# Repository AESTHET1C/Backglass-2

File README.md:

# Backglass 2 Pinball Controller Board

An Arduino Uno-compatible unified control board tailored to the Eli Whitney Museum 2017 summer pinball project.

The board contains the following hardware:

* Microchip ATmega8U2/16U2 (serial communication and code upload)
* Microchip ATmega328P (user code)
* Microchip ATmega48PB (audio/visual coprocessing)
* 4-character 7 segment display
* 2 analogue inputs (for reflectance sensors)
* 5 digital inputs (with integrated pull-ups)
* 3 current-limited LED outputs
* 1 PWM-controlled motor output
* 1 speaker output
* Micro USB interface
* 2.7 - 6.5 volt power input

All features of the board, with the exception of the motor, can be powered via USB.

-----

A user-oriented code library can be found here: <https://github.com/AESTHET1C/Backglass-2-Library/>

The coprocessor firmware can be found here: <https://github.com/AESTHET1C/Backglass-2-Firmware/>

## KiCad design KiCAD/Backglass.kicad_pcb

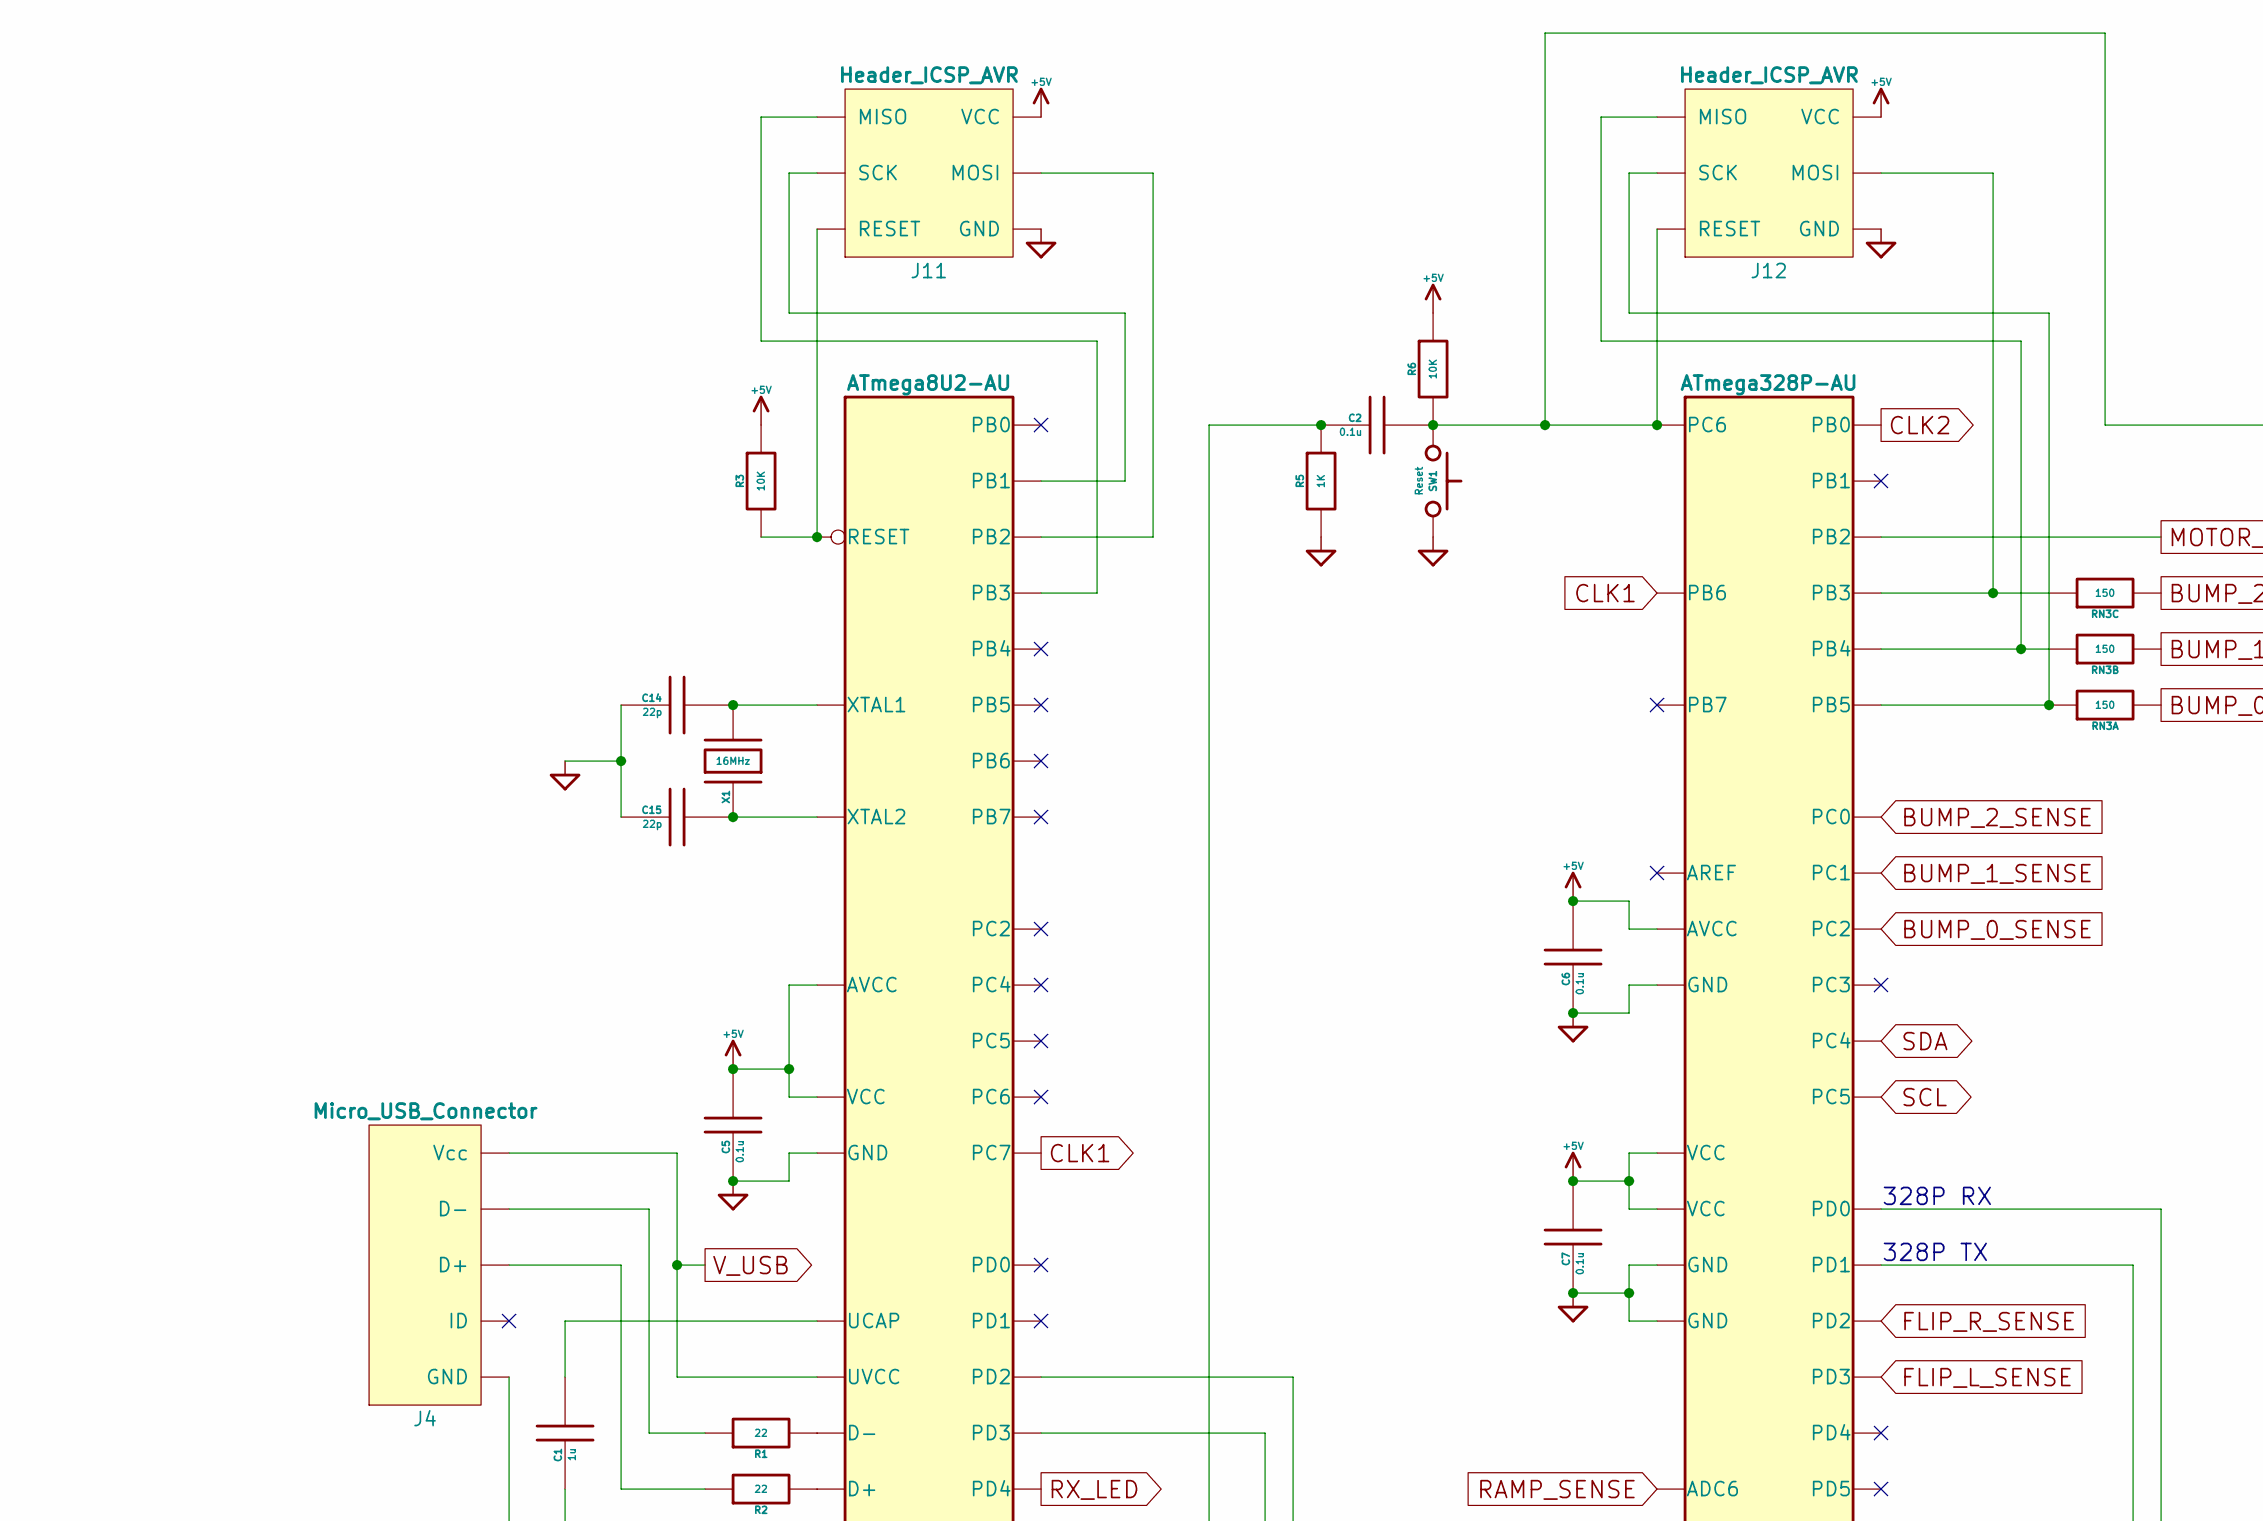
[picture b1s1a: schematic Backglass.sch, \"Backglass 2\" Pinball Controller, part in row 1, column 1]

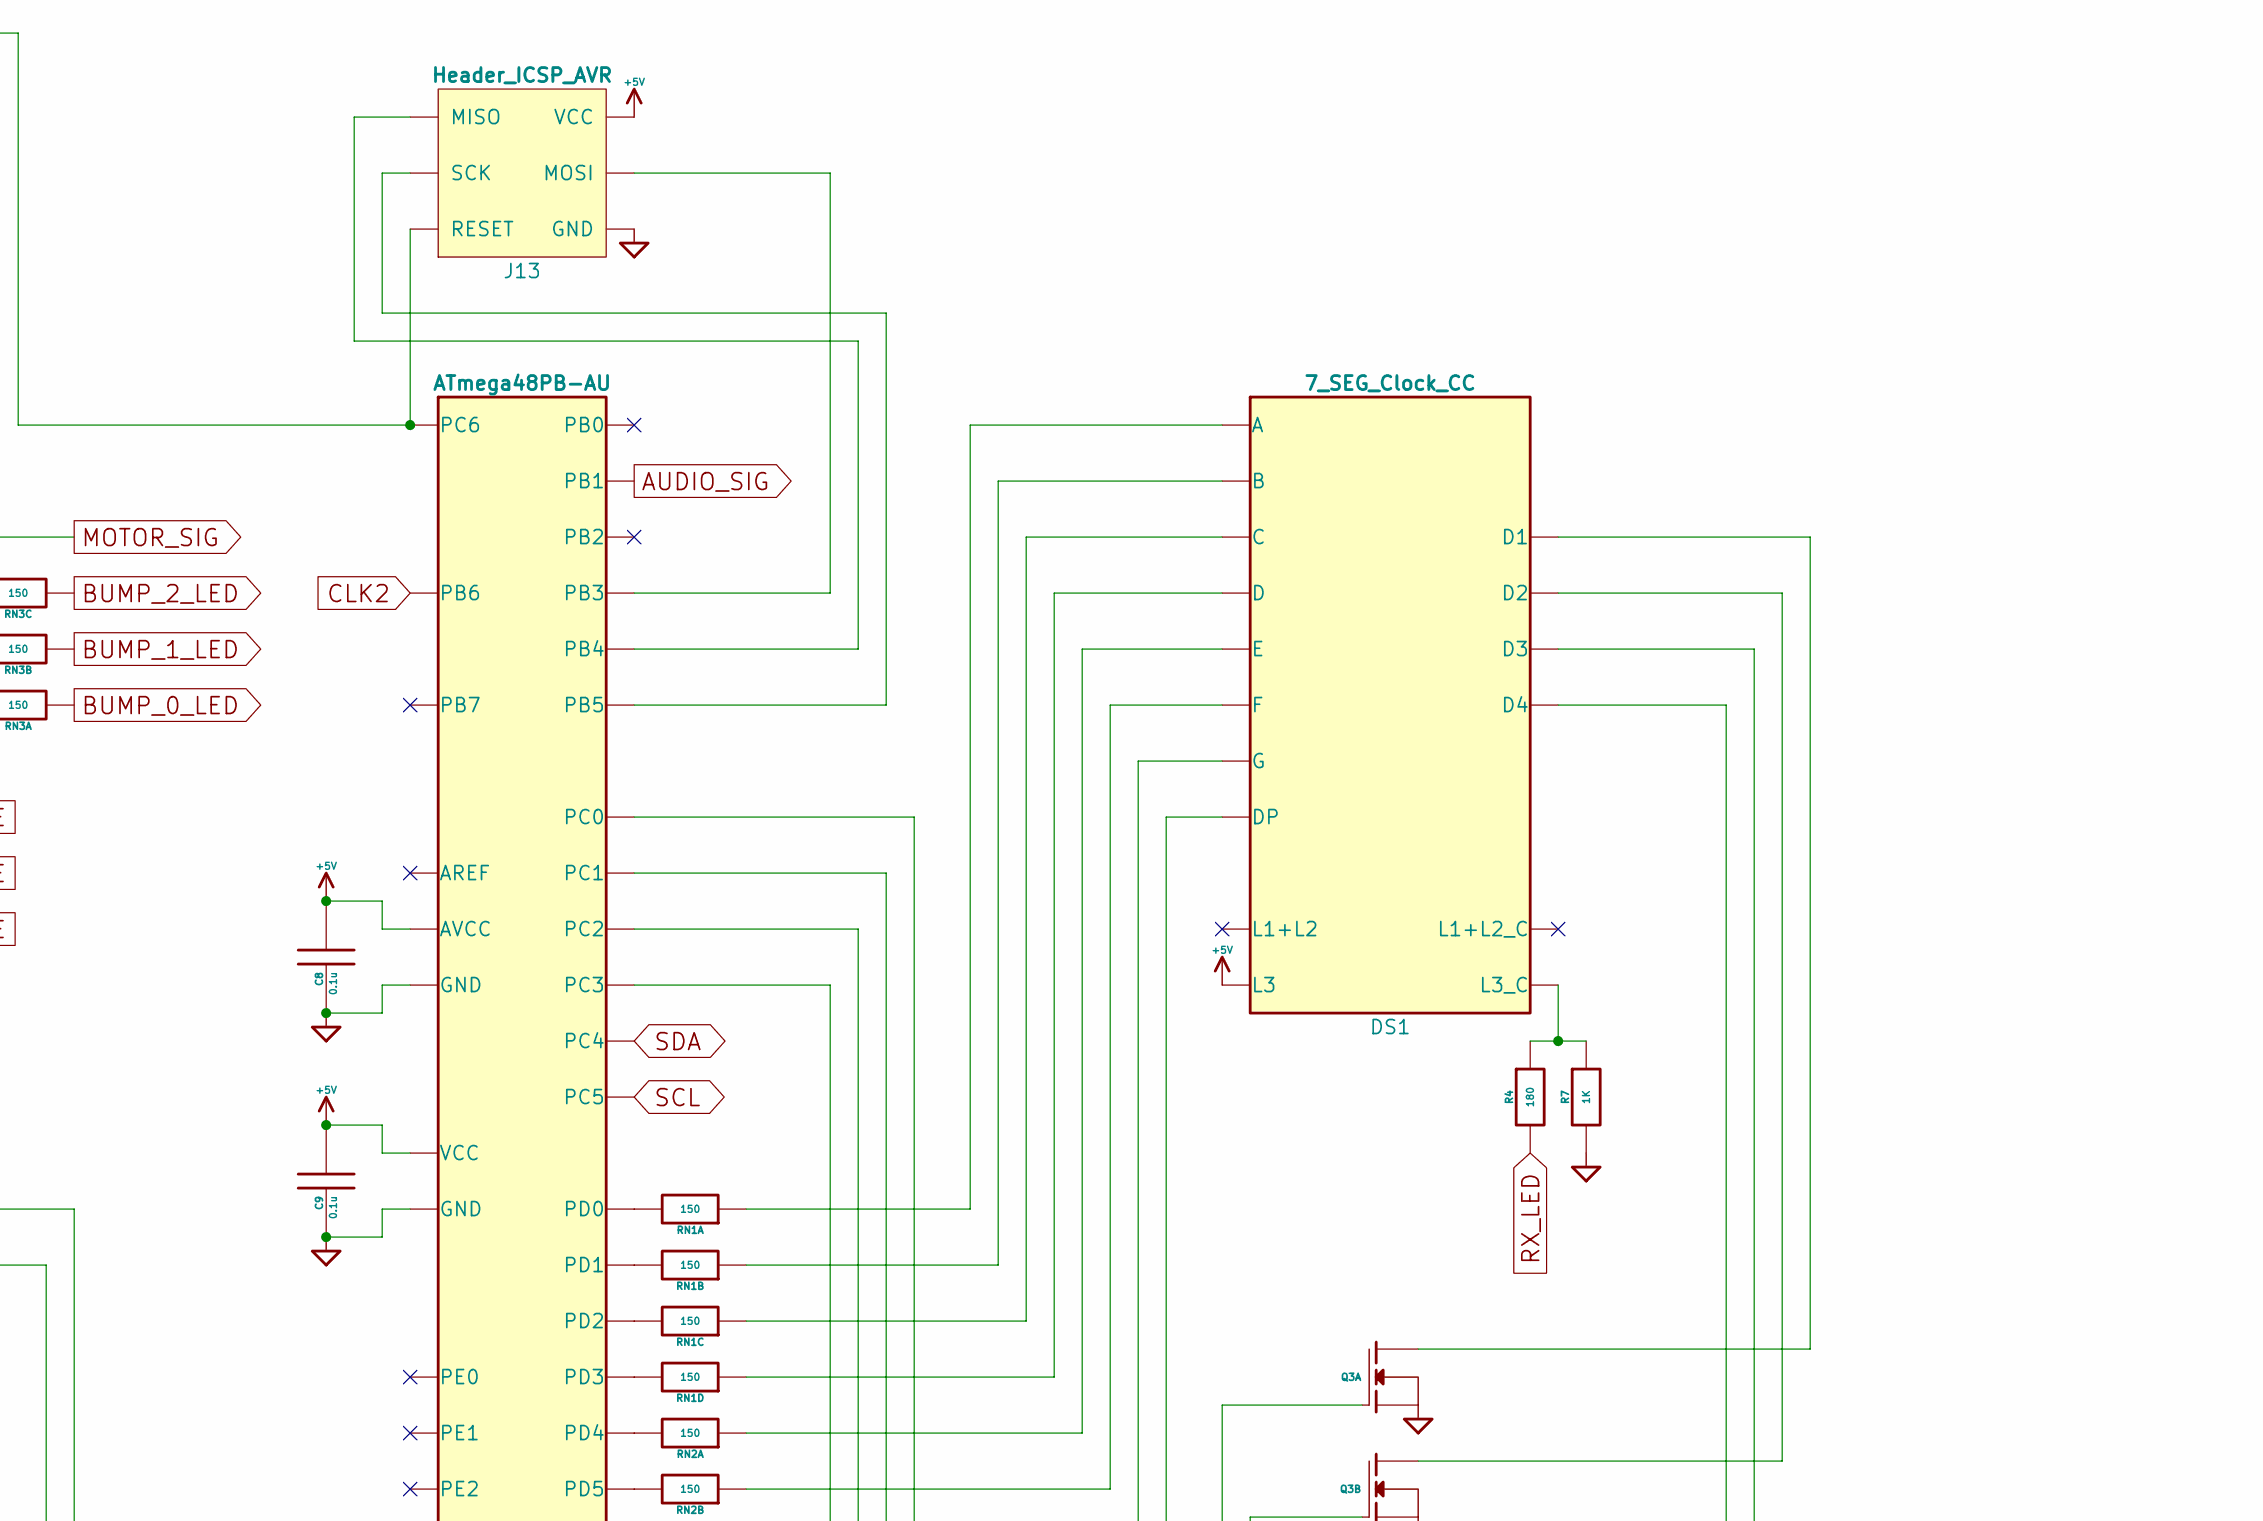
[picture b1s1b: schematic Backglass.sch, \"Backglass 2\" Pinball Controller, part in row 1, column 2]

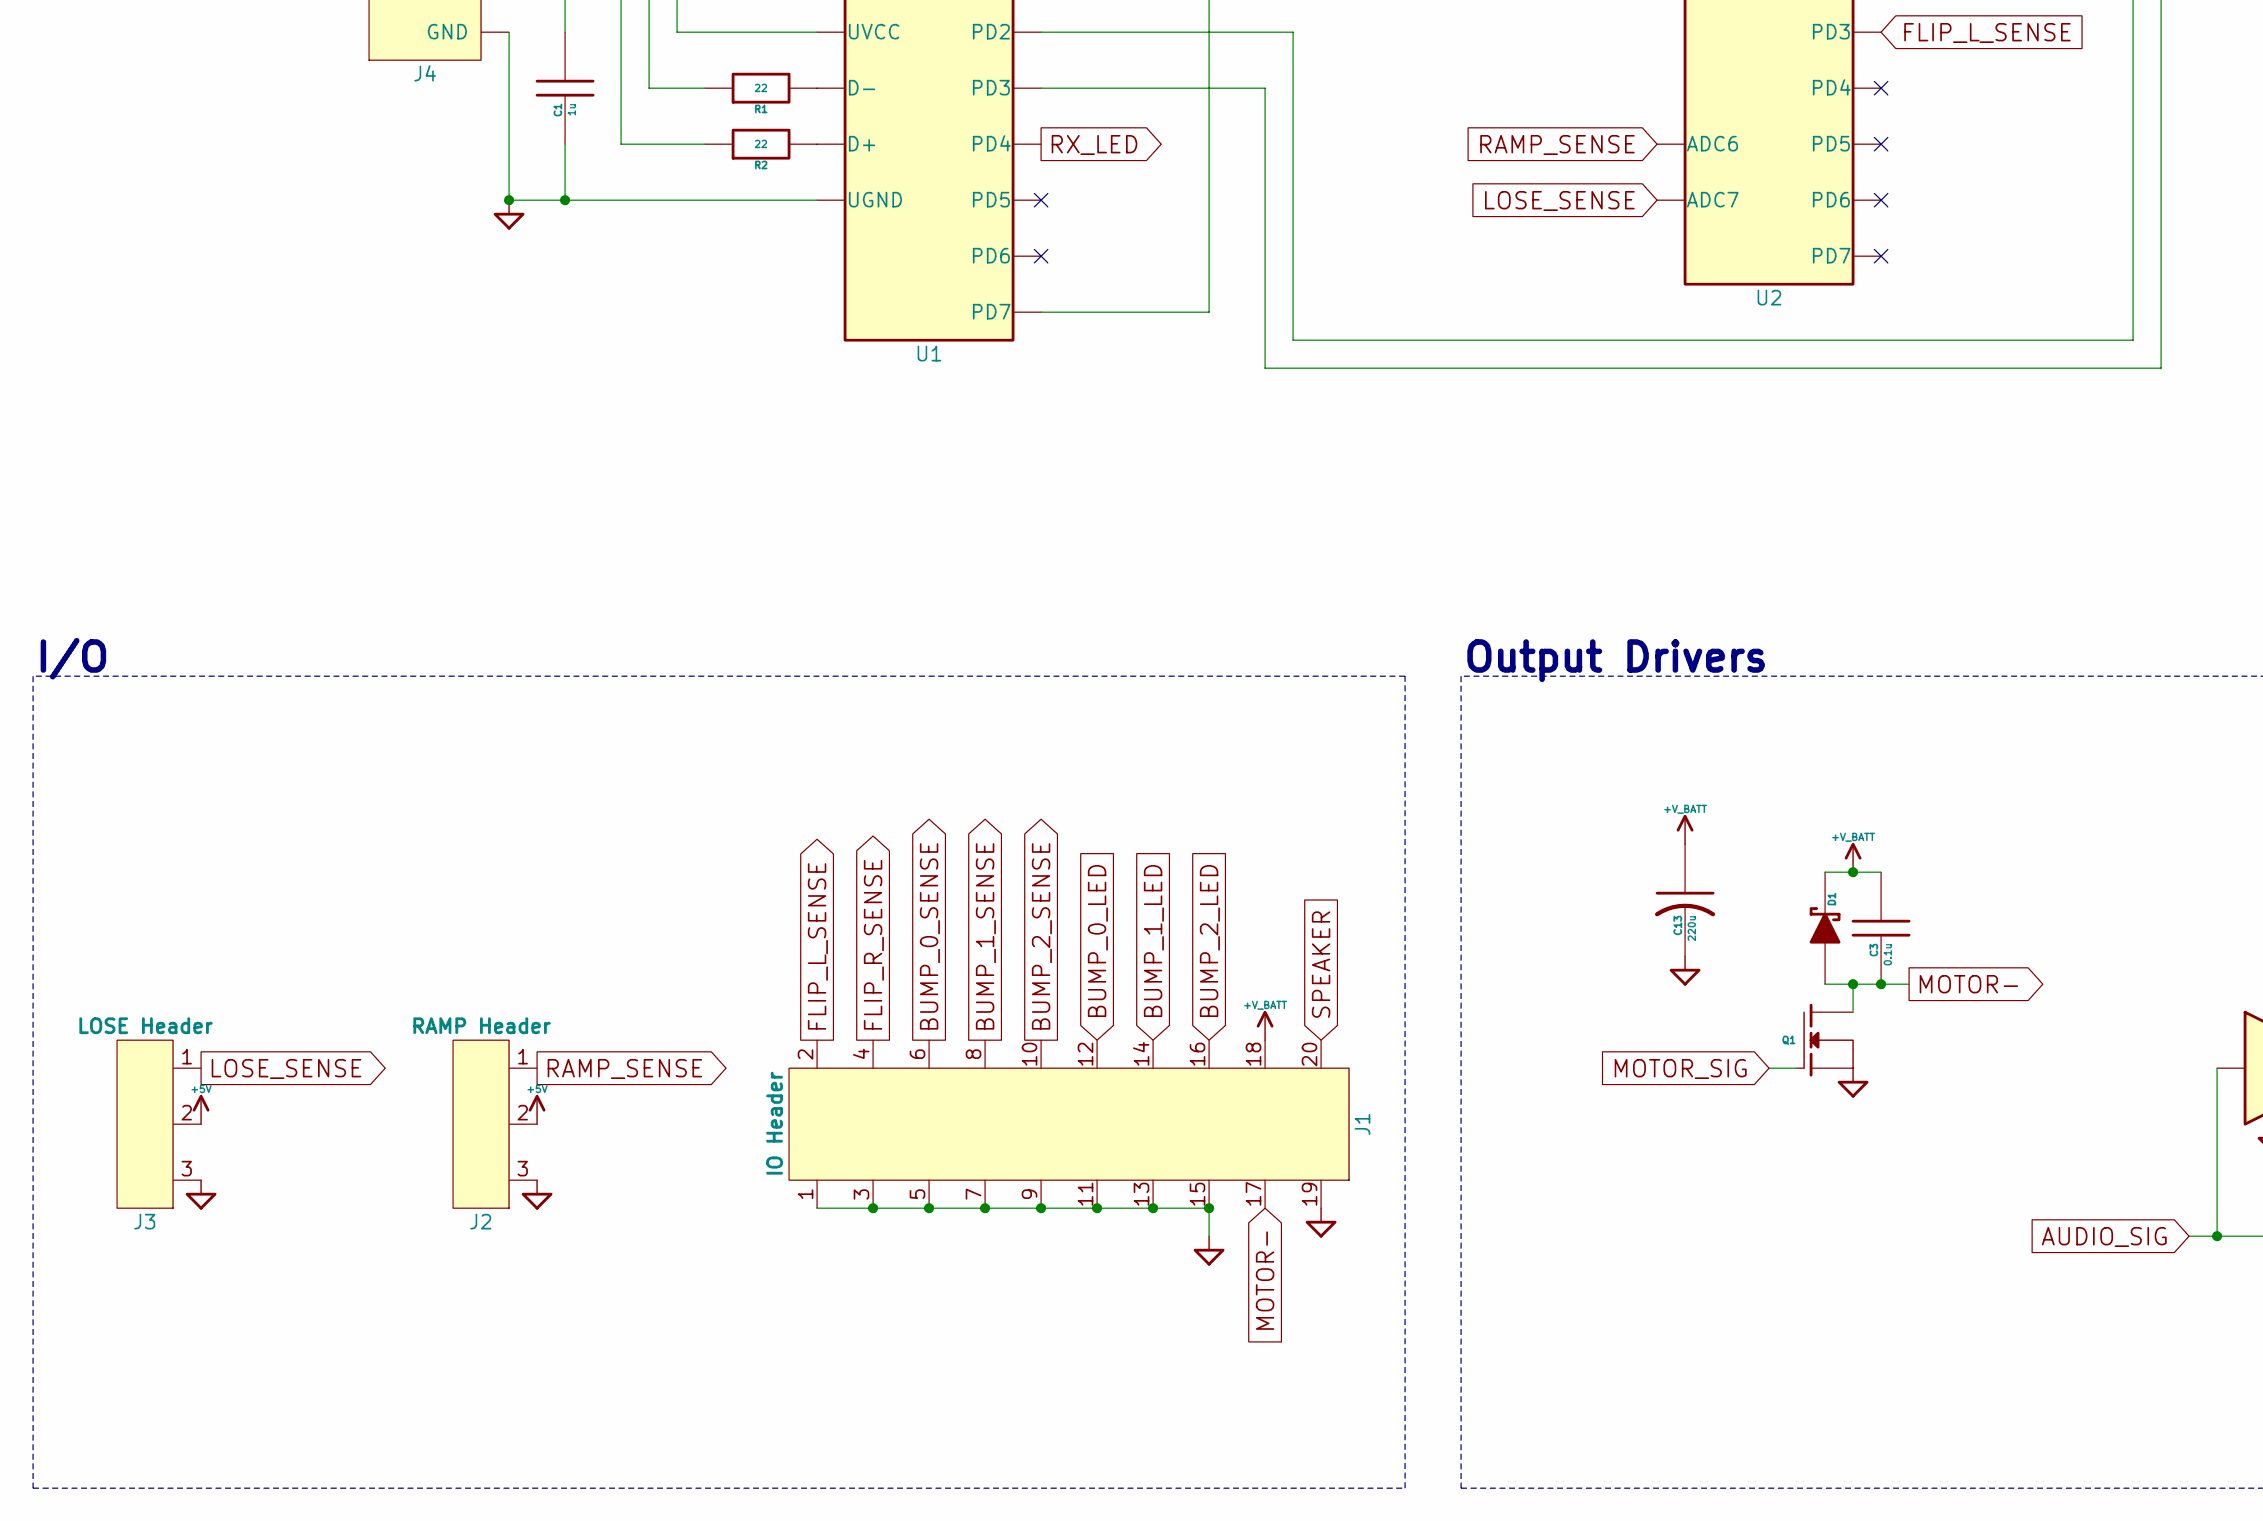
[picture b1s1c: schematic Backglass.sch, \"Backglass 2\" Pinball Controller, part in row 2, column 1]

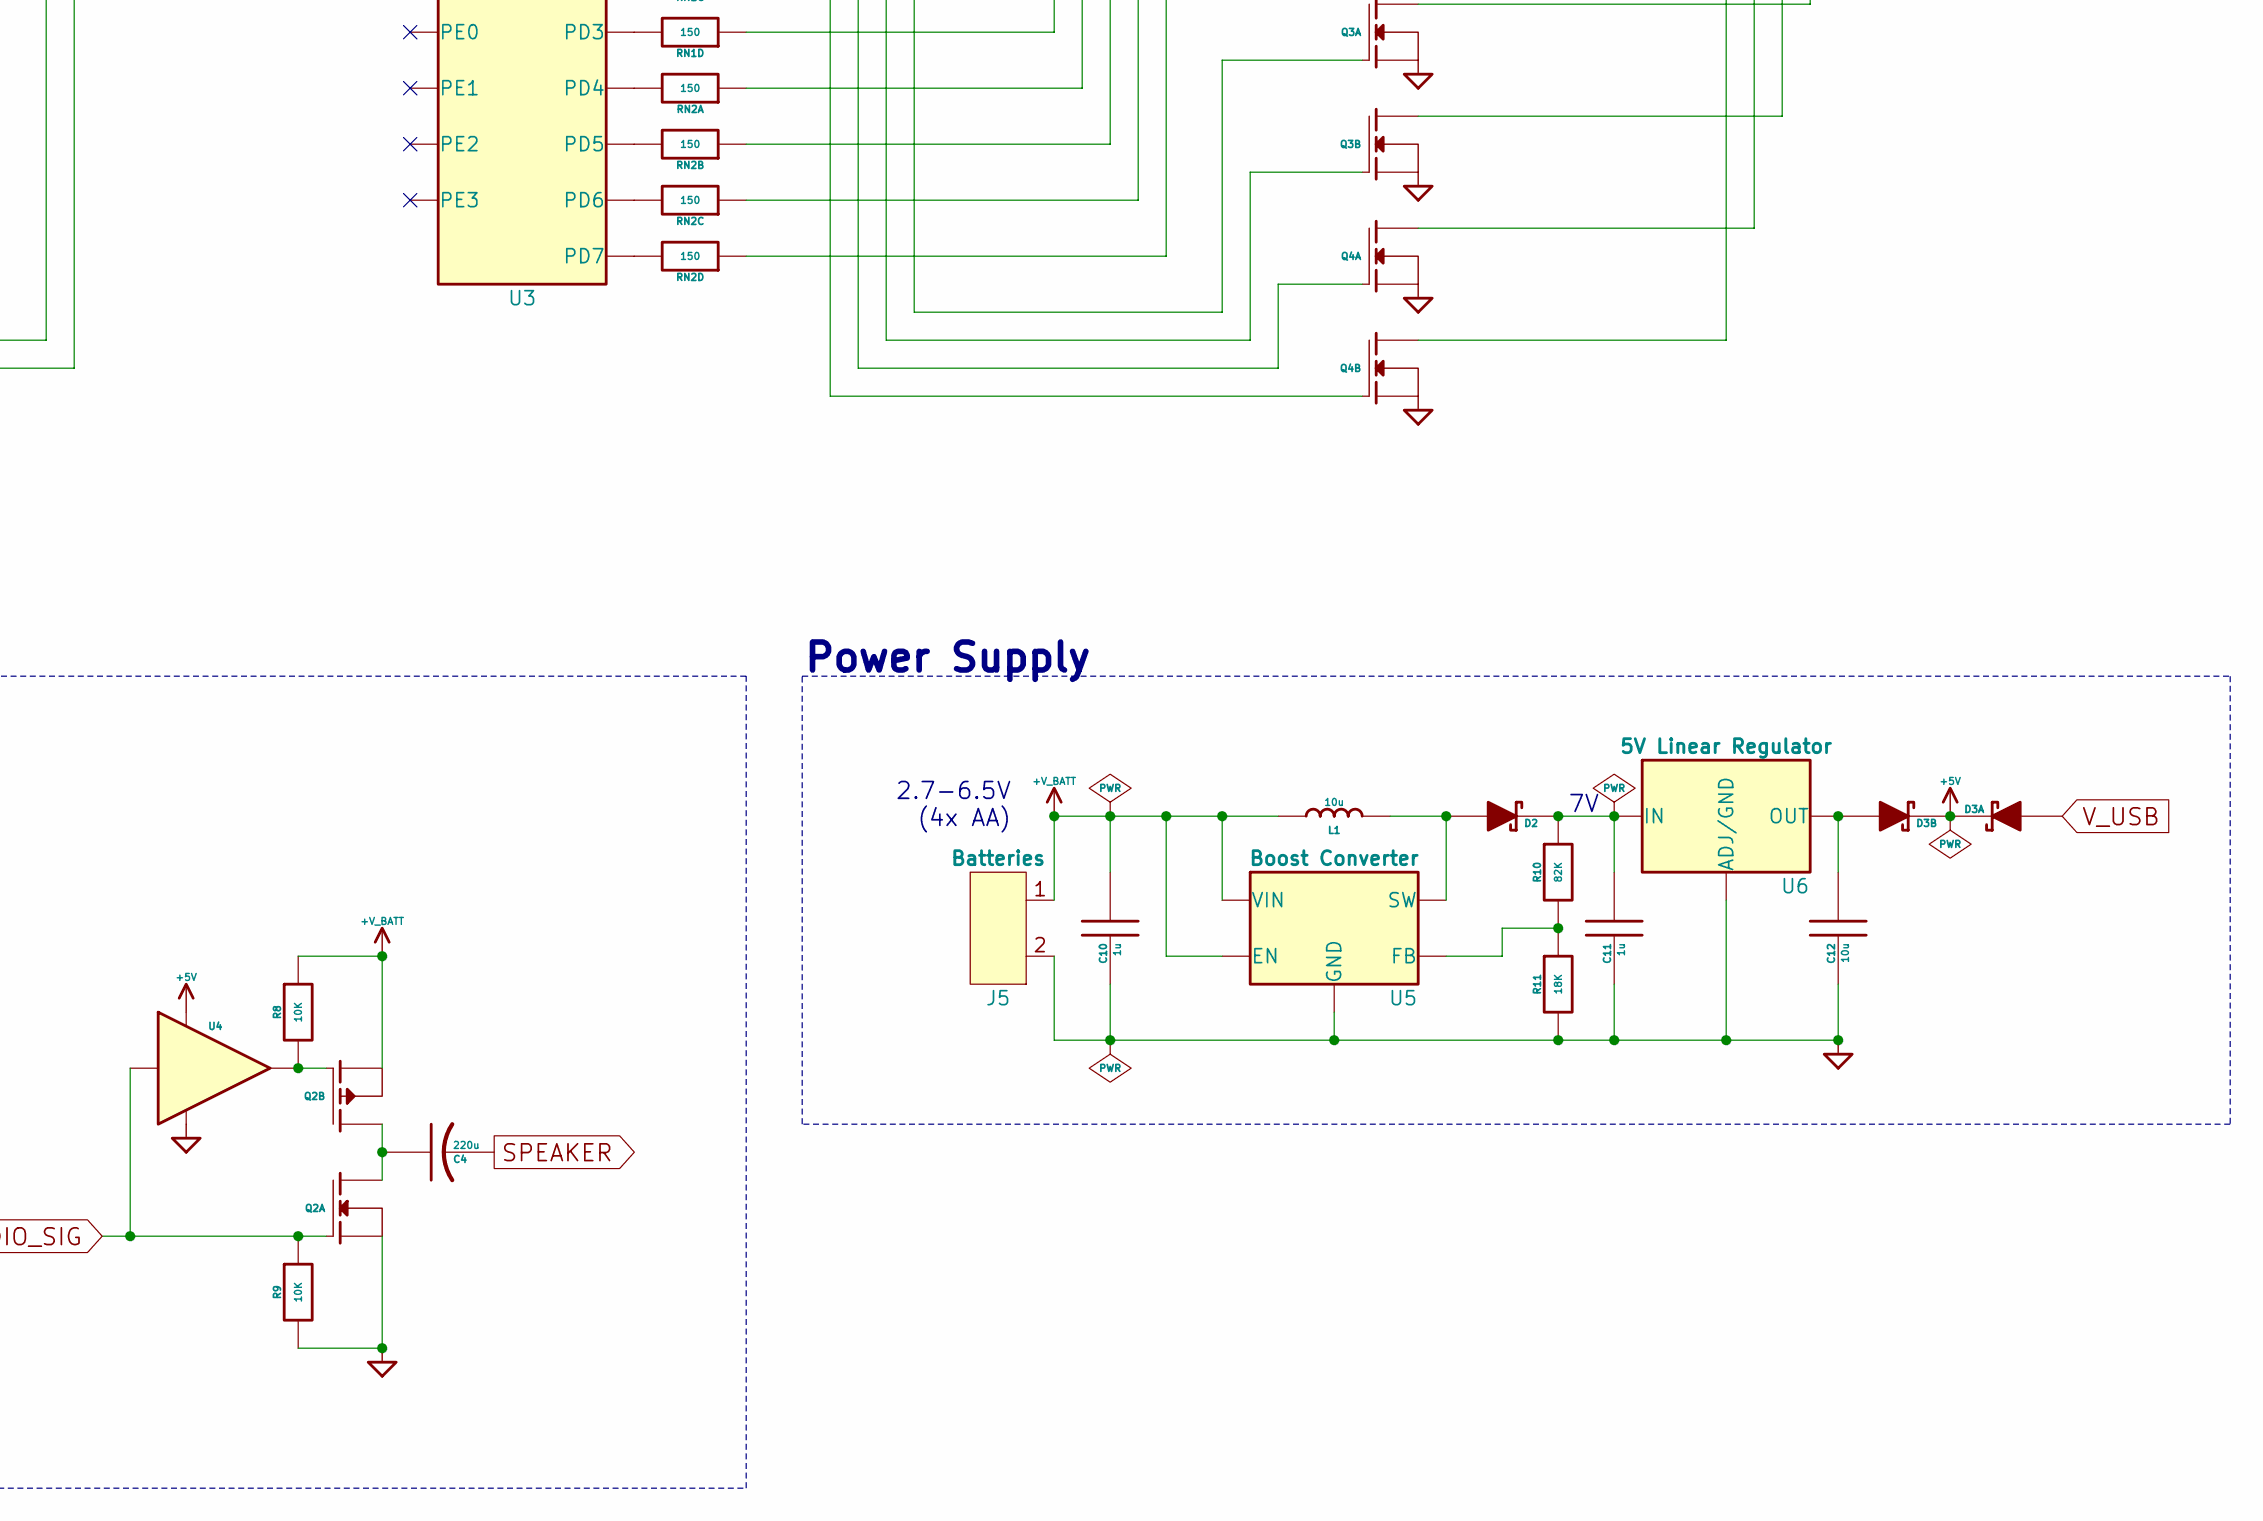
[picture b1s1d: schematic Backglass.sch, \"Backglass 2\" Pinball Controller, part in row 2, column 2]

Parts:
C1, C10, C11: 1u; 1608
C2, C3, C5, C6, C7, C8, C9: 0.1u; 1608
C4, C13: 220u; C_6.3-2.5mm
C12: 10u; 2012
C14, C15: 22p; 1608
D1, D2: D_Schottky; SOT-23-3_A-C
D3: D_Schottky_Dual_CC; SOT-23-3_AAC
DS1: 7_SEG_Clock_CC; TDCx10xxM
J1: IO Header; 10x2_0.1in
J2: RAMP Header; 3x1_0.1in
J3: LOSE Header; 3x1_0.1in
J4: Micro_USB_Connector; Molex_1051640001
J5: Batteries; 2x1_0.1in
J11, J12, J13: Header_ICSP_AVR; AVR_ICSP_0.05in
L1: 10u; 3225
Q1: MOSFET_N_E; SOT-23-3_GSD
Q2: MOSFET_N_E+P_E; SOT-23-6_G1-S2-G2-D2-S1-D1
Q3, Q4: MOSFET_N_E_Dual; TSSOP-6_S1-G1-D2-S2-G2-D1
R1, R2: 22; 1608
R3, R6, R8, R9: 10K; 1608
R4: 180; 1608
R5, R7: 1K; 1608
R10: 82K; 1608
R11: 18K; 1608
RN1, RN2, RN3: 150; Array_4x1608_Convex_NP
SW1: Reset; Tact_Switch_6mm
U1: ATmega8U2-AU; TQFP-32
U2: ATmega328P-AU; TQFP-32
U3: ATmega48PB-AU; TQFP-32
U4: 74LVC1G07GW/V; SOT-23-5
U5: Boost Converter; SOT-23-5
U6: 5V Linear Regulator; SOT-223-4
X1: 16MHz; 3.2x2.5_SMD_CRYSTAL

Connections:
+5V: C5.2, C6.2, C7.2, C8.2, C9.2, D3.C, DS1.9 (L3), J2.2, J3.2, J11.2 (VCC), J12.2 (VCC), J13.2 (VCC), R3.1, R6.1, U1.4 (VCC), U1.32 (AVCC), U2.4 (VCC), U2.6 (VCC), U2.18 (AVCC), U3.4 (VCC), U3.18 (AVCC), U4.5 (Vcc)
+V_BATT: C3.2, C10.2, C13.1, D1.C, J1.18, J5.1, L1.1, Q2.S2, R8.1, U5.4 (EN), U5.5 (VIN)
AUDIO_SIG: Q2.G1, R9.1, U3.13 (PB1), U4.2 (A)
BUMP_0_LED: J1.12, RN3.8
BUMP_0_SENSE: J1.6, U2.25 (PC2)
BUMP_1_LED: J1.14, RN3.7
BUMP_1_SENSE: J1.8, U2.24 (PC1)
BUMP_2_LED: J1.16, RN3.6
BUMP_2_SENSE: J1.10, U2.23 (PC0)
CLK1: U1.22 (PC7), U2.7 (PB6)
CLK2: U2.12 (PB0), U3.7 (PB6)
FLIP_L_SENSE: J1.2, U2.1 (PD3)
FLIP_R_SENSE: J1.4, U2.32 (PD2)
GND: C1.1, C5.1, C6.1, C7.1, C8.1, C9.1, C10.1, C11.1, C12.1, C13.2, C14.1, C15.1, J1.1, J1.3, J1.5, J1.7, J1.9, J1.11, J1.13, J1.15, J1.19, J2.3, J3.3, J4.5 (GND), J5.2, J11.6 (GND), J12.6 (GND), J13.6 (GND), Q1.S, Q2.S1, Q3.S1, Q3.S2, Q4.S1, Q4.S2, R5.2, R7.2, R9.2, R11.2, SW1.2 (NO), U1.3 (GND), U1.28 (UGND), U2.3 (GND), U2.5 (GND), U2.21 (GND), U3.5 (GND), U3.21 (GND), U4.1, U4.3 (GND), U5.2 (GND), U6.1 (ADJ/GND)
MOTOR-: C3.1, D1.A, J1.17, Q1.D
MOTOR_SIG: Q1.G, U2.14 (PB2)
unnamed: C1.2, U1.27 (UCAP)
unnamed: C2.1, R5.1, U1.13 (PD7)
unnamed: C2.2, J12.5 (RESET), J13.5 (RESET), R6.2, SW1.1 (C), U2.29 (PC6), U3.29 (PC6)
unnamed: C4.1, Q2.D1, Q2.D2
unnamed: C11.2, D2.C, R10.1, U6.3 (IN)
unnamed: C12.2, D3.A2, U6.2 (OUT), U6.4
unnamed: C14.2, U1.1 (XTAL1), X1.2
unnamed: C15.2, U1.2 (XTAL2), X1.1
unnamed: D2.A, L1.2, U5.1 (SW)
unnamed: DS1.1 (D1), Q3.D1
unnamed: DS1.2 (D2), Q3.D2
unnamed: DS1.3 (D), RN1.4
unnamed: DS1.5 (E), RN2.1
unnamed: DS1.6 (D3), Q4.D1
unnamed: DS1.7 (DP), RN2.4
unnamed: DS1.8 (D4), Q4.D2
unnamed: DS1.10 (L3_C), R4.1, R7.1
unnamed: DS1.11 (F), RN2.2
unnamed: DS1.13 (C), RN1.3
unnamed: DS1.14 (A), RN1.1
unnamed: DS1.15 (G), RN2.3
unnamed: DS1.16 (B), RN1.2
unnamed: J4.2 (D-), R1.1
unnamed: J4.3 (D+), R2.1
unnamed: J11.1 (MISO), U1.17 (PB3)
unnamed: J11.3 (SCK), U1.15 (PB1)
unnamed: J11.4 (MOSI), U1.16 (PB2)
unnamed: J11.5 (RESET), R3.2, U1.24 (RESET)
unnamed: J12.1 (MISO), RN3.2, U2.16 (PB4)
unnamed: J12.3 (SCK), RN3.1, U2.17 (PB5)
unnamed: J12.4 (MOSI), RN3.3, U2.15 (PB3)
unnamed: J13.1 (MISO), U3.16 (PB4)
unnamed: J13.3 (SCK), U3.17 (PB5)
unnamed: J13.4 (MOSI), U3.15 (PB3)
unnamed: Q2.G2, R8.2, U4.4 (Y)
unnamed: Q3.G1, U3.23 (PC0)
unnamed: Q3.G2, U3.24 (PC1)
unnamed: Q4.G1, U3.25 (PC2)
unnamed: Q4.G2, U3.26 (PC3)
unnamed: R1.2, U1.30 (D-)
unnamed: R2.2, U1.29 (D+)
unnamed: R10.2, R11.1, U5.3 (FB)
unnamed: RN1.5, U3.1 (PD3)
unnamed: RN1.6, U3.32 (PD2)
unnamed: RN1.7, U3.31 (PD1)
unnamed: RN1.8, U3.30 (PD0)
unnamed: RN2.5, U3.11 (PD7)
unnamed: RN2.6, U3.10 (PD6)
unnamed: RN2.7, U3.9 (PD5)
unnamed: RN2.8, U3.2 (PD4)
unnamed: U1.8 (PD2), U2.31 (PD1)
unnamed: U1.9 (PD3), U2.30 (PD0)
OUT_SENSE: J3.1, U2.22 (ADC7)
RAMP_SENSE: J2.1, U2.19 (ADC6)
RX_LED: R4.2, U1.10 (PD4)
SCL: U2.28 (PC5), U3.28 (PC5)
SDA: U2.27 (PC4), U3.27 (PC4)
SPEAKER: C4.2, J1.20
V_USB: D3.A1, J4.1 (Vcc), U1.31 (UVCC)

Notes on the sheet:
328P RX
328P TX
2.7-6.5V (4x AA)
Power Supply
I/O
Output Drivers

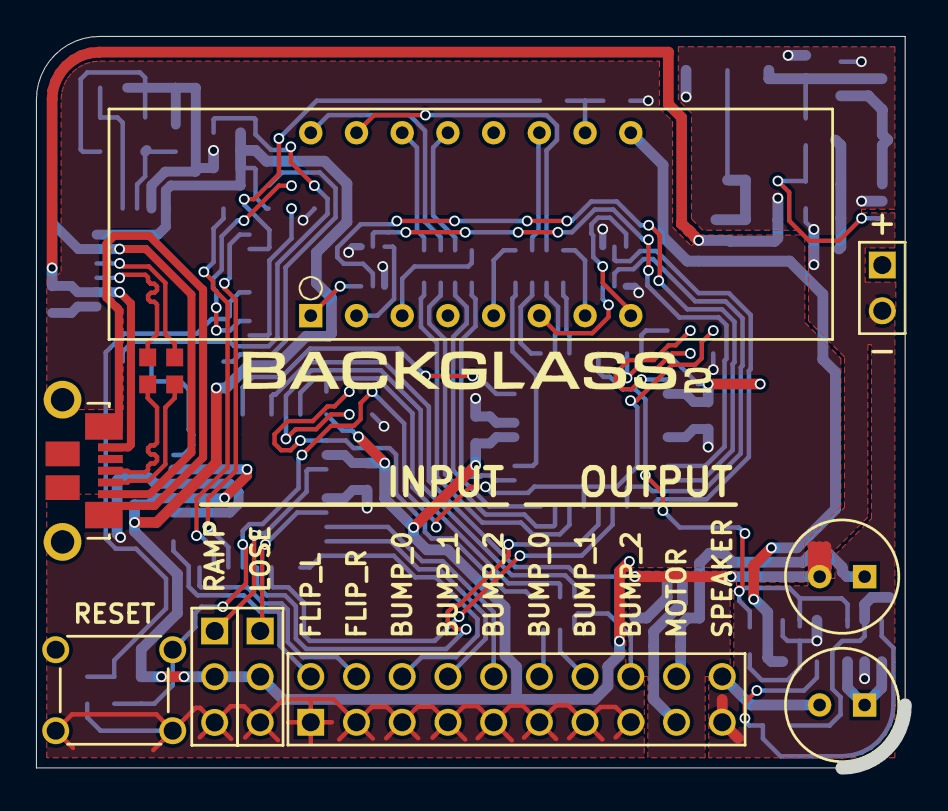
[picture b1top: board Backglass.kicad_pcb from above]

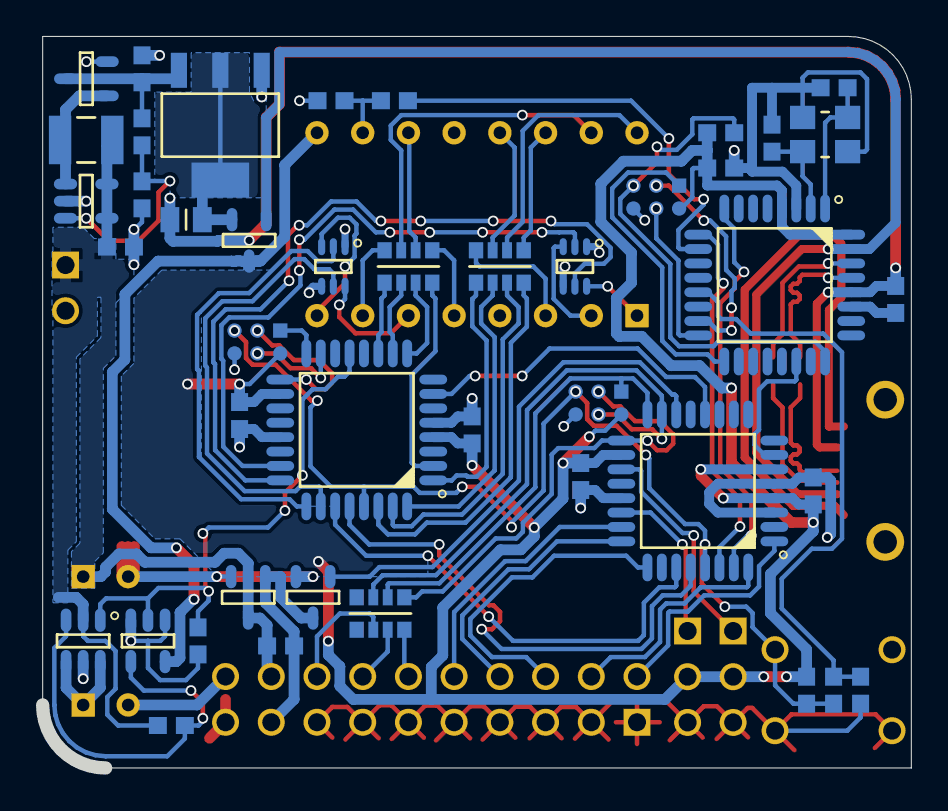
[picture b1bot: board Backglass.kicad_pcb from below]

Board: 2 copper layers, 47.9 x 40.3 mm, 54 parts (43 on the bottom side), 75 nets.

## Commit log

2017-04-19 :space_invader: Added .gitattributes & .gitignore files
2017-04-19 Initial upload
    Added basic KiCAD files, gerbers, schematic PDF, and vague readme
    describing the board.
2017-04-19 Added link to firmware in readme
2017-05-05 Added link to library
2017-05-05 Fixed audio output, reduced power consumption
    Removed half-bridge and associated components, modified resistor values
    to drive LEDs dimmer (and now within power specs for the 48PB).
2017-06-21 Updated readme
    Clarification on the display type
